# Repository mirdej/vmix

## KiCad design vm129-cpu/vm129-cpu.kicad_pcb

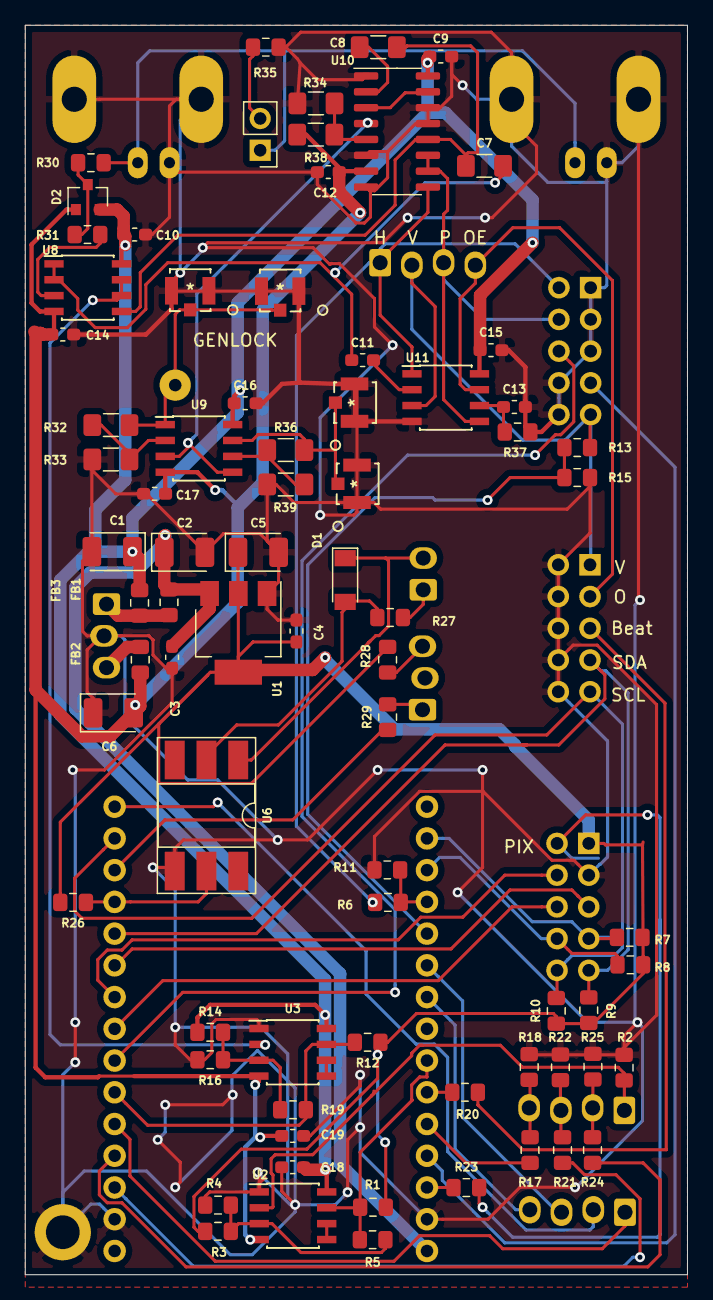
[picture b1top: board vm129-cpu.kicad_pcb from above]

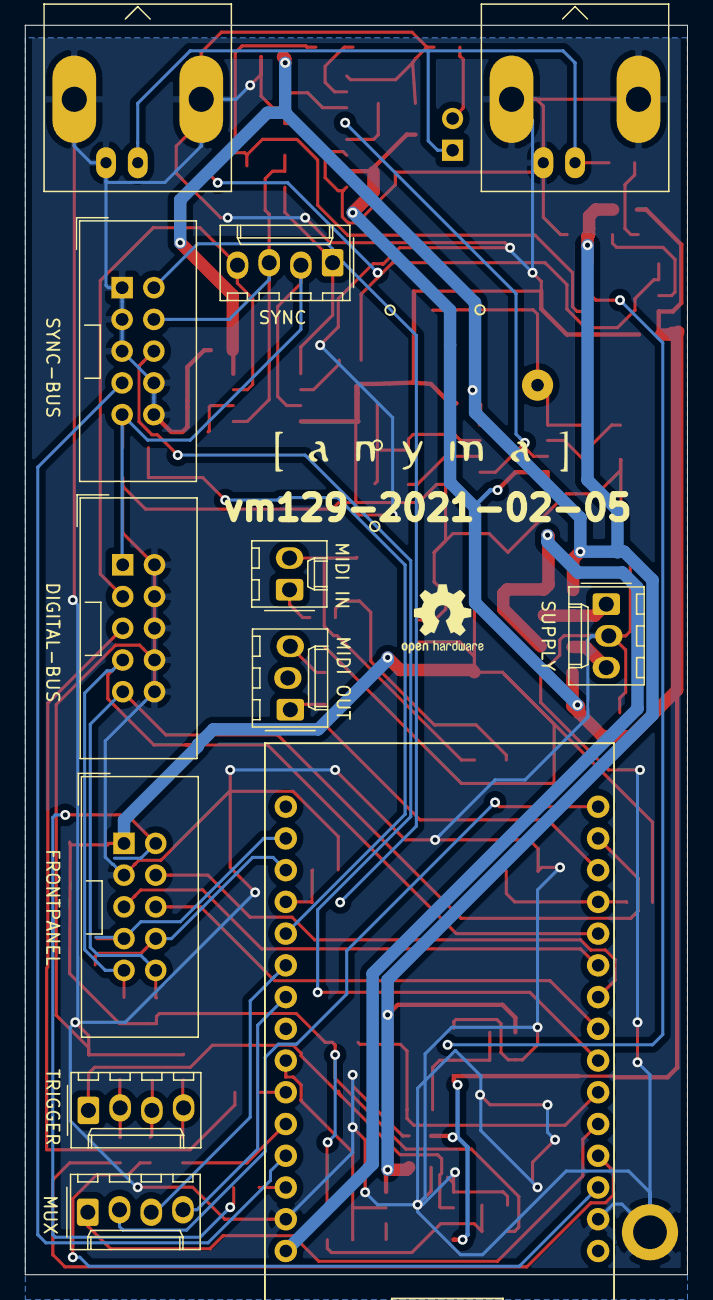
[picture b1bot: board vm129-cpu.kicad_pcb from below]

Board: 2 copper layers, 53.0 x 100.0 mm, 92 parts (14 on the bottom side), 67 nets.

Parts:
C1, C6: 10u; CP_EIA-3528-21_Kemet-B_Pad1.50x2.35mm_HandSolder
C2, C5: CP; CP_EIA-3528-21_Kemet-B_Pad1.50x2.35mm_HandSolder
C3, C4, C9, C10, C11, C12, C13, C14, C15, C16, C17, C18, C19: 100n; C_0603_1608Metric_Pad1.05x0.95mm_HandSolder
C7, C8: 1u; C_1206_3216Metric_Pad1.42x1.75mm_HandSolder
D1: D; D_MiniMELF
D2: BAT54S; SOT-23
FB1, FB2, FB3: Ferrite_Bead; L_0805_2012Metric_Pad1.15x1.40mm_HandSolder
H1: MountingHole_Pad; MountingHole_2.7mm_M2.5_ISO7380_Pad
J1: Supply; Molex_KK-254_AE-6410-03A_1x03_P2.54mm_Vertical
J2: mux; Molex_KK-254_AE-6410-04A_1x04_P2.54mm_Vertical
J3: triggers; Molex_KK-254_AE-6410-04A_1x04_P2.54mm_Vertical
J4: Syncbus; IDC-Header_2x05_P2.54mm_Vertical
J6: Digitalbus; IDC-Header_2x05_P2.54mm_Vertical
J7: Frontpanel; IDC-Header_2x05_P2.54mm_Vertical
J8: Sync-Bus; Molex_KK-254_AE-6410-04A_1x04_P2.54mm_Vertical
J9: MIDI-IN; Molex_KK-254_AE-6410-02A_1x02_P2.54mm_Vertical
J10: MIDI-OUT; Molex_KK-254_AE-6410-03A_1x03_P2.54mm_Vertical
J11: GENLOCK; Solderpad_1mm
J12, J14: Conn_Coaxial; BNC_MOLEX_0731000080_Horizontal
J13, J15, J17, J18: UMCC; TE_UMCC_2337019-1
J16: Conn_01x02; PinHeader_1x02_P2.54mm_Vertical
R1, R7, R8, R9, R10: 4k7; R_0805_2012Metric_Pad1.15x1.40mm_HandSolder
R2: 10k; R_0805_2012Metric_Pad1.15x1.40mm_HandSolder
R3, R18, R22, R25: 1k; R_0805_2012Metric_Pad1.15x1.40mm_HandSolder
R4: 180; R_0805_2012Metric_Pad1.15x1.40mm_HandSolder
R5, R19: 510k; R_0805_2012Metric_Pad1.15x1.40mm_HandSolder
R6, R13: 2k; R_0805_2012Metric_Pad1.15x1.40mm_HandSolder
R11, R12, R14, R15: 3k; R_0805_2012Metric_Pad1.15x1.40mm_HandSolder
R16: 300; R_0805_2012Metric_Pad1.15x1.40mm_HandSolder
R17, R21, R24: 2k2; R_0805_2012Metric_Pad1.15x1.40mm_HandSolder
R20, R23: 100; R_0805_2012Metric_Pad1.15x1.40mm_HandSolder
R26: 47k; R_0805_2012Metric_Pad1.15x1.40mm_HandSolder
R27, R28, R29: 220; R_0805_2012Metric_Pad1.15x1.40mm_HandSolder
R30, R31, R35: 75; R_0805_2012Metric_Pad1.15x1.40mm_HandSolder
R32, R33, R36, R39: 200; R_1206_3216Metric_Pad1.42x1.75mm_HandSolder
R34: 150; R_1206_3216Metric_Pad1.42x1.75mm_HandSolder
R37: 680k; R_0805_2012Metric_Pad1.15x1.40mm_HandSolder
R38: 4k7; R_1206_3216Metric_Pad1.42x1.75mm_HandSolder
U1: LD1117S33TR_SOT223; SOT-223-3_TabPin2
U2, U3: LM311; SOIC-8_3.9x4.9mm_P1.27mm
U4: ESP32-DevBoard; ESP32_Devboard
U5: LOGO; logo_anyma
U6: 4N25; DIP-6_W8.89mm_SMDSocket_LongPads
U7: LOGO; OSHW-Logo2_7.3x6mm_SilkScreen
U8: LMH6643; SOIC-8_3.9x4.9mm_P1.27mm
U9: MAX4392; SOIC-8_3.9x4.9mm_P1.27mm
U10: 4053; SOIC-16_3.9x9.9mm_P1.27mm
U11: LM1881; SOIC-8_3.9x4.9mm_P1.27mm

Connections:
3V3: C4.1, C5.1, J7.1, R1.1, R3.1, R7.1, R8.1, R9.1, R10.1, R12.1, R26.2, R28.1, U1.2
+5V: C1.1, C9.1, C10.2, C15.1, C16.1, C18.1, D2.2, FB1.2, R14.1, U2.8, U3.8, U8.8, U9.8, U10.16, U11.8
-5V: C6.2, C12.2, C14.1, C17.2, C19.2, D2.1, FB2.2, R38.1, U2.4, U3.4, U8.4, U9.4, U10.7
/Genlock/burst_only: U10.3, U10.15
/Genlock/genlock_in: J12.1, J14.1, J16.1, R30.1
/Genlock/synctip: R34.1, R38.2, U10.5
/btn_clk: J7.4, U4.24
/btn_data: J7.5, U4.25
/btn_latch: J7.6, U4.23
/enc_a: J7.7, R7.2, U4.2
/enc_b: J7.8, R8.2, U4.3
/hysnc_3v3: R6.1, R11.1, U4.4
/mux1: J2.1, U4.20
/mux2: J2.2, U4.30
/mux3: J2.3, U4.6
/mux4: J2.4, U4.7
/pix: J7.2, R23.2
/rx: R26.1, U4.27, U6.5
/scl: J6.9, J7.10, R10.2, U4.29
/sda: J6.7, J7.9, R9.2, U4.26
/supply+: FB1.1, FB3.1, J1.1
/trig1: J3.2, R24.2, R25.1
/trig1_3v3: R24.1, U4.19
/trig2: J3.3, R21.2, R22.1
/trig2_3v3: R21.1, U4.18
/trig3: J3.4, R17.2, R18.1
/trig3_3v3: R17.1, U4.11
/trig_in: J3.1, R2.1, U2.2
/trig_in_3v3: R1.2, R5.1, U2.7, U4.9
/tx: R29.1, U4.28
/video_read: R12.2, R19.1, U3.7, U4.21
/vsync_3v3: R13.1, R15.1, U4.5
GND: C1.2, C2.2, C3.2, C4.2, C5.2, C6.1, C9.2, C10.1, C12.1, C13.2, C14.2, C15.2, C16.2, C17.1, C18.2, C19.1, H1.1, J1.2, J4.1, J4.3, J4.5, J4.8, J4.10, J6.2, J6.4, J6.6, J6.8, J6.10, J7.3, J12.2, J13.2, J13.3, J14.2, J15.2, J15.3, J17.2, J17.3, J18.2, J18.3, R2.2, R4.2, R11.2, R15.2, R16.2, R18.2, R22.2, R25.2, R33.1, R34.2, R35.2, R37.2, R39.1, U1.1, U2.1, U3.1, U4.14, U4.17, U6.4, U10.1, U10.6, U10.8, U10.13, U10.14, U11.4
unnamed: C7.1, C8.2, U8.5, U10.12
unnamed: C8.1, U10.2
unnamed: C11.1, U11.2
unnamed: C7.2, C11.2, U8.1, U8.2
unnamed: C13.1, R37.1, U11.6
unnamed: D1.1, J9.2, U6.1
unnamed: D1.2, R27.1, U6.2
unnamed: D2.3, R30.2, R31.1
unnamed: FB2.1, J1.3
unnamed: J9.1, R27.2
unnamed: J10.1, R29.2
unnamed: J10.3, R28.2
unnamed: J11.1, J13.1, J15.1, R32.2, U9.1
unnamed: J16.2, R35.1
unnamed: J17.1, J18.1, R36.2, U9.7
unnamed: R3.2, R4.1, R5.2, U2.3
unnamed: R14.2, R16.1, R19.2, U3.3
unnamed: R20.1, U4.10
unnamed: R23.1, U4.13
unnamed: R31.2, U8.3
unnamed: R32.1, R33.2, U9.2
unnamed: R36.1, R39.2, U9.6
unnamed: U2.5, U2.6
unnamed: U3.5, U3.6
unnamed: U9.3, U9.5, U10.4
VCC: C2.1, C3.1, FB3.2, U1.3, U4.15
beatsync: J6.5, R20.2
clamped_genlock: U3.2, U8.6, U8.7
hsync: J4.2, J8.1, R6.2, U10.9, U11.1
oddeven: J6.3, J8.4, U11.7
porch: J4.4, J8.3, U10.10, U10.11, U11.5
synkietxt: J4.6, U4.22
synkietxt_enable: J4.7, U4.12
vsync: J4.9, J6.1, J8.2, R13.2, U11.3

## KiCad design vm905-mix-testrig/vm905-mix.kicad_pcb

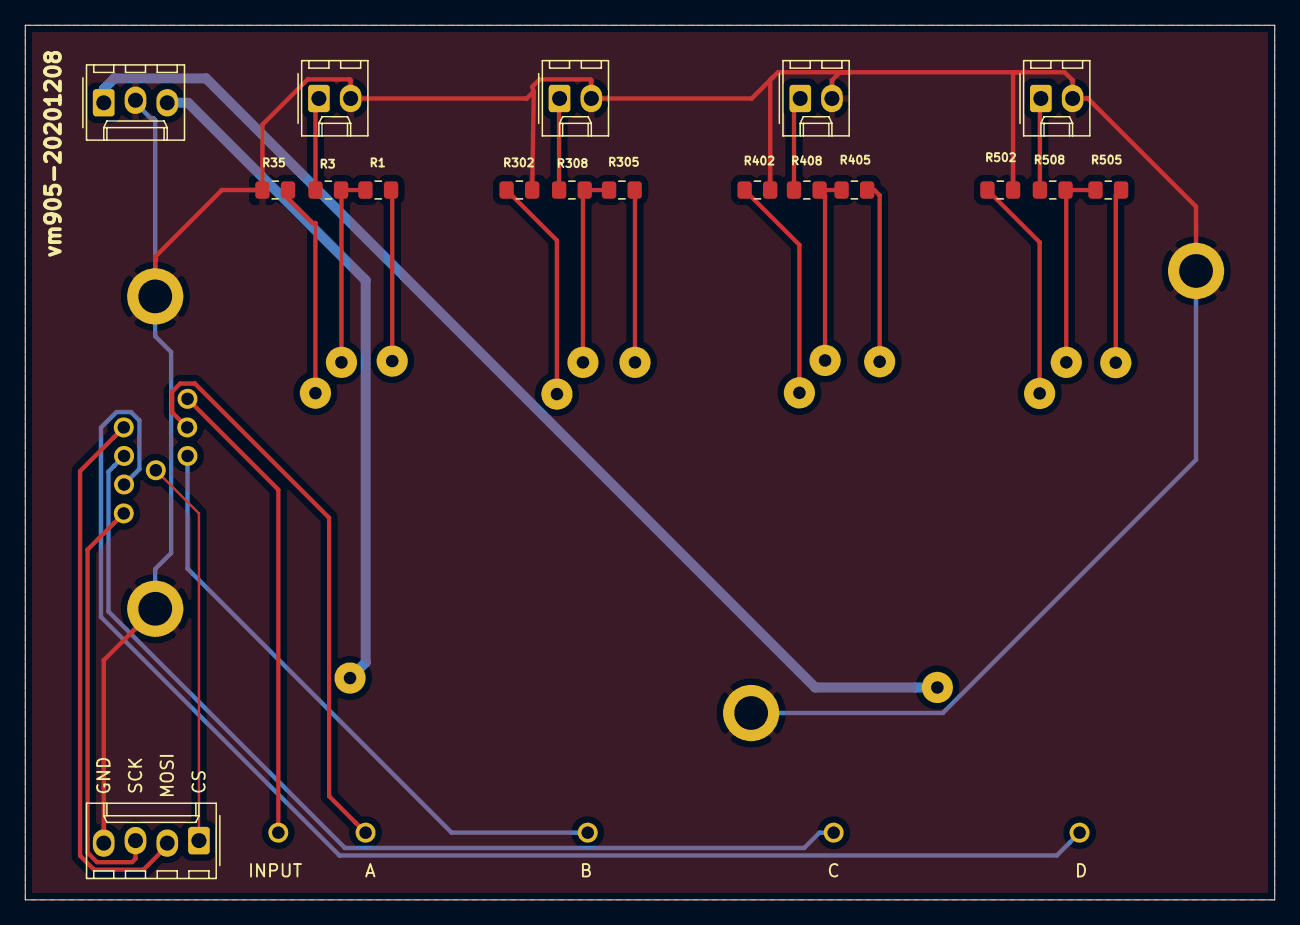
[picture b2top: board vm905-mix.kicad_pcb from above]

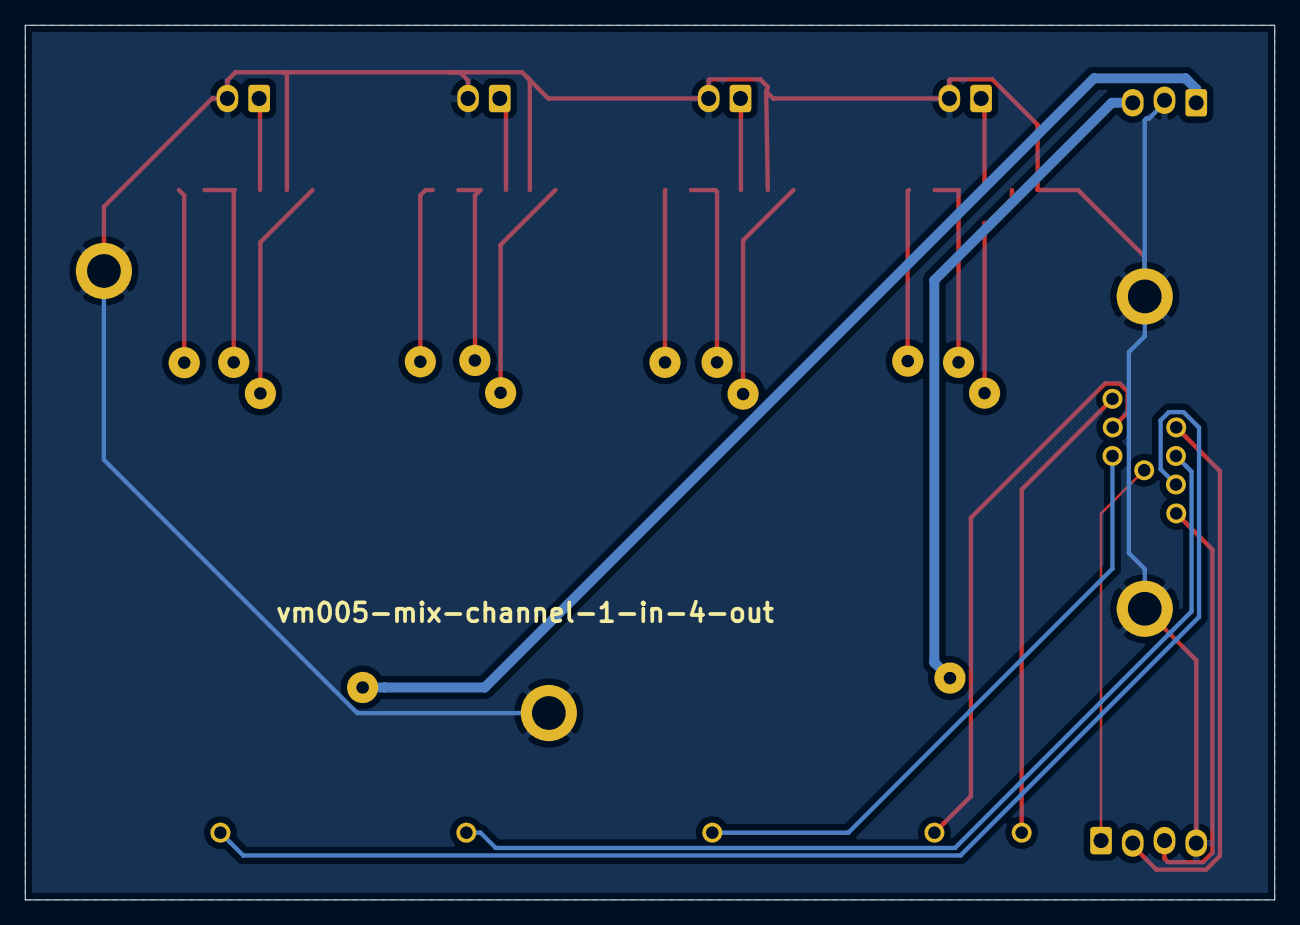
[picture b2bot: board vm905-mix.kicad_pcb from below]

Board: 2 copper layers, 100.0 x 70.0 mm, 49 parts (2 on the bottom side), 27 nets.

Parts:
H1, H2, H3, H4: MountingHole_Pad; MountingHole_2.7mm_M2.5_ISO7380_Pad
J1: Conn_01x03_Female; Molex_KK-254_AE-6410-03A_1x03_P2.54mm_Vertical
J2, J301, J401, J501: Conn_01x02; Molex_KK-254_AE-6410-02A_1x02_P2.54mm_Vertical
J3: Conn_01x04_Male; Molex_KK-254_AE-6410-04A_1x04_P2.54mm_Vertical
R1, R35, R302, R305, R402, R405, R502, R505: (560); R_0805_2012Metric_Pad1.15x1.40mm_HandSolder
R3, R308, R408, R508: (75); R_0805_2012Metric_Pad1.15x1.40mm_HandSolder
TP1, TP2, TP11, TP12, TP13, TP14, TP15, TP16, TP17, TP18, TP19, TP20, TP21, TP22: TestPoint; Solderpad_1mm
TP3, TP4, TP5, TP6, TP7, TP8, TP9, TP10, TP23, TP24, TP25, TP26, TP27: TestPoint; testpad-small

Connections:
+5V: J1.1, TP1.1
-5V: J1.3, TP2.1
/cv_a: TP4.1, TP24.1
/cv_b: TP5.1, TP25.1
/cv_c: TP8.1, TP26.1
/cv_d: TP9.1, TP27.1
/dac_select: J3.1, TP6.1
/input: TP3.1, TP23.1
/mosi: J3.2, TP7.1
/sck: J3.3, TP10.1
GND: H1.1, H2.1, H3.1, H4.1, J1.2, J2.2, J3.4, J301.2, J401.2, J501.2, R35.1, R302.1, R402.1, R502.1
unnamed: J2.1, R3.2
unnamed: J301.1, R308.2
unnamed: J401.1, R408.2
unnamed: J501.1, R508.2
unnamed: R1.1, R3.1, TP22.1
unnamed: R1.2, TP21.1
unnamed: R35.2, TP20.1
unnamed: R302.2, TP11.1
unnamed: R305.1, R308.1, TP13.1
unnamed: R305.2, TP12.1
unnamed: R402.2, TP14.1
unnamed: R405.1, R408.1, TP16.1
unnamed: R405.2, TP15.1
unnamed: R502.2, TP17.1
unnamed: R505.1, R508.1, TP19.1
unnamed: R505.2, TP18.1

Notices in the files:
parts and their libraries:
Copyright 2016 Accelerated Designs. All rights reserved.
